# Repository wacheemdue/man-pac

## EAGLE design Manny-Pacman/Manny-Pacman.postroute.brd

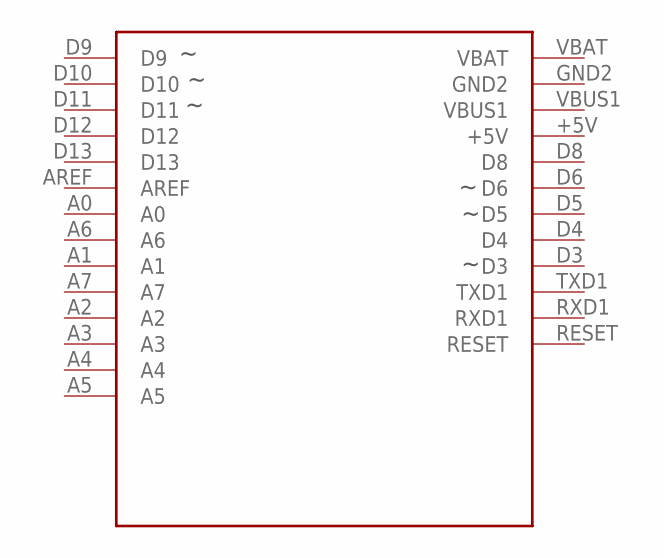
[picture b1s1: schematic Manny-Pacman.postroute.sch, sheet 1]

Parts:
U2: ADAFRUIT-PRO-TRINKET-5V-NOFTDI

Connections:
+5V_0_BRAIN: U2.+5V; also elsewhere on the board
A0_0_BRAIN: U2.A0
A1_0_BRAIN: U2.A1
A2_0_BRAIN: U2.A2
A3_0_BRAIN: U2.A3
A4_0_BRAIN: U2.A4
A5_0_BRAIN: U2.A5
A6_0_BRAIN: U2.A6
A7_0_BRAIN: U2.A7
AREF_0_BRAIN: U2.AREF
D3_0_BRAIN: U2.D3; also elsewhere on the board
D4_0_BRAIN: U2.D4; also elsewhere on the board
D5_0_BRAIN: U2.D5; also elsewhere on the board
D6_0_BRAIN: U2.D6; also elsewhere on the board
D8_0_BRAIN: U2.D8; also elsewhere on the board
D9_0_BRAIN: U2.D9; also elsewhere on the board
D10_0_BRAIN: U2.D10; also elsewhere on the board
D11_0_BRAIN: U2.D11
D12_0_BRAIN: U2.D12
D13_0_BRAIN: U2.D13
GND_0_BRAIN: U2.GND2; also elsewhere on the board
POS_1_BATTERY: U2.VBAT; also elsewhere on the board
RESET_0_BRAIN: U2.RESET
RXD1_0_BRAIN: U2.RXD1
TXD1_0_BRAIN: U2.TXD1
VBUS1_0_BRAIN: U2.VBUS1

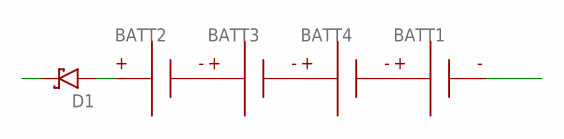
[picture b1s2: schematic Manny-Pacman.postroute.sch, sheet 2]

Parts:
BATT1, BATT2, BATT3, BATT4: BATTERY-AA-CLIP; BATTERY-AA-BK-92
D1: RESOLVED-DIODE-SCHOTTKY_TH-DO-41-AND-DO-204AL; DIOAD1125W78L520D270_HS; MPN 1N5817

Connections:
GND_0_BRAIN: BATT1.N1 (N), BATT1.N2 (N); also elsewhere on the board
unnamed: BATT2.N1 (N), BATT2.N2 (N), BATT3.P1, BATT3.P2
unnamed: BATT3.N1 (N), BATT3.N2 (N), BATT4.P1, BATT4.P2
unnamed: BATT1.P1, BATT1.P2, BATT4.N1 (N), BATT4.N2 (N)
unnamed: BATT2.P1, BATT2.P2, D1.A
POS_1_BATTERY: D1.C; also elsewhere on the board

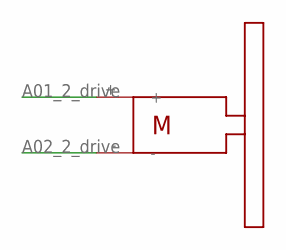
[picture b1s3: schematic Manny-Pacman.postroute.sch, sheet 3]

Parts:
U4: SOLARBOTICS_GM2; SOLARBOTICS_G2

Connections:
A01_2_DRIVE: U4.+; also elsewhere on the board
A02_2_DRIVE: U4.-; also elsewhere on the board

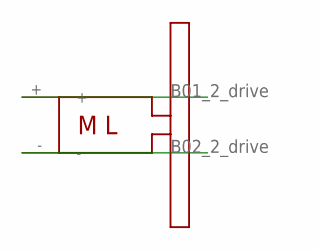
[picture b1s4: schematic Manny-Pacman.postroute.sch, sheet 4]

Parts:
U1: SOLARBOTICS_GM2_LEFT; SOLARBOTICS_G2_LEFT

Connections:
B01_2_DRIVE: U1.+; also elsewhere on the board
B02_2_DRIVE: U1.-; also elsewhere on the board

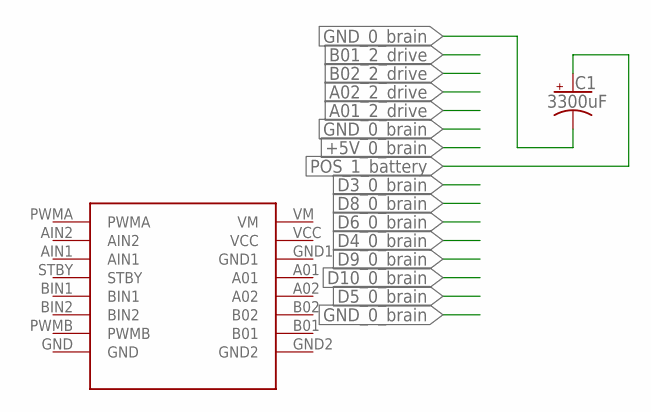
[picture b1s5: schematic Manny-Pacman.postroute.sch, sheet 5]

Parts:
C1: 3300uF; CAPPRD750W80D1600H2200P; MPN ECA-1EM332
U3: SPARKFUN_DUAL_MOTOR_DRIVER-BOB; SPARKFUN_DUAL_MOTOR_DRIVER

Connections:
+5V_0_BRAIN: U3.VCC; also elsewhere on the board
A01_2_DRIVE: U3.A01; also elsewhere on the board
A02_2_DRIVE: U3.A02; also elsewhere on the board
B01_2_DRIVE: U3.B01; also elsewhere on the board
B02_2_DRIVE: U3.B02; also elsewhere on the board
D3_0_BRAIN: U3.PWMA; also elsewhere on the board
D4_0_BRAIN: U3.STBY; also elsewhere on the board
D5_0_BRAIN: U3.PWMB; also elsewhere on the board
D6_0_BRAIN: U3.AIN1; also elsewhere on the board
D8_0_BRAIN: U3.AIN2; also elsewhere on the board
D9_0_BRAIN: U3.BIN1; also elsewhere on the board
D10_0_BRAIN: U3.BIN2; also elsewhere on the board
GND_0_BRAIN: C1.2 (-), U3.GND, U3.GND1, U3.GND2; also elsewhere on the board
POS_1_BATTERY: C1.1 (+), U3.VM; also elsewhere on the board

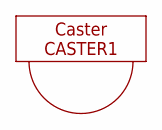
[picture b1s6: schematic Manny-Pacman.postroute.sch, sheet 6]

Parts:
CASTER1: CASTERADAFRUIT-3/4IN; ADAFRUIT-3/4IN-CASTER

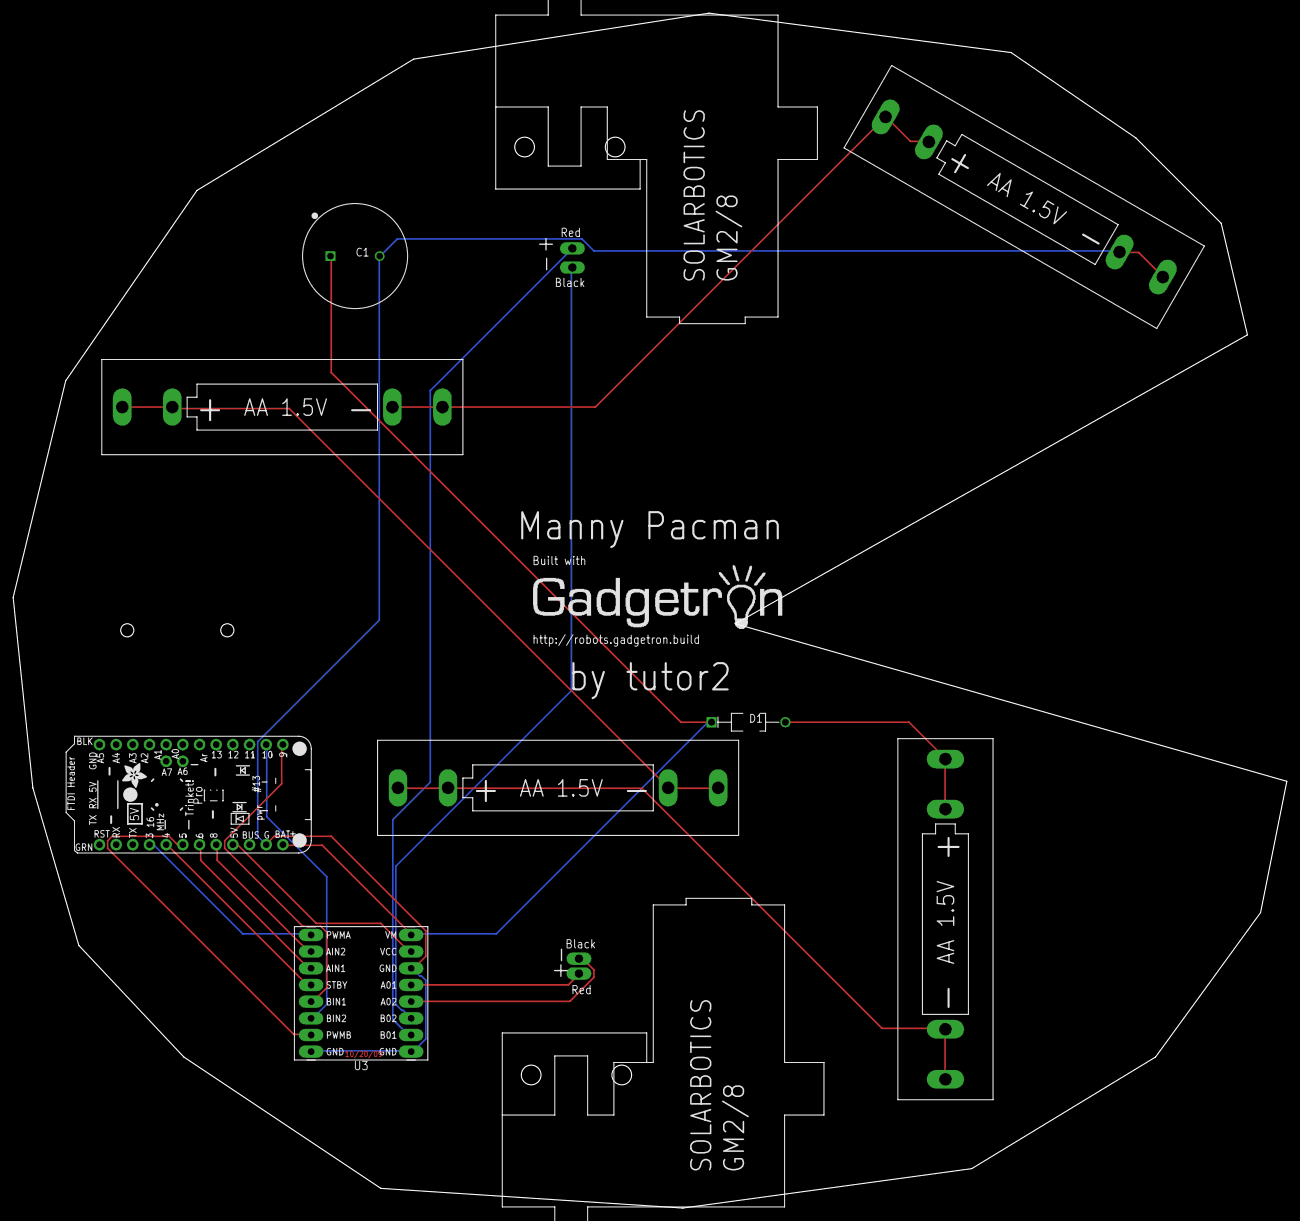
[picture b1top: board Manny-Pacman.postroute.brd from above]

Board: 2 copper layers, 194.0 x 182.0 mm, 12 parts (0 on the bottom side), 18 nets.

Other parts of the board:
LOGO: BUILT_WITH_GADGETRON
